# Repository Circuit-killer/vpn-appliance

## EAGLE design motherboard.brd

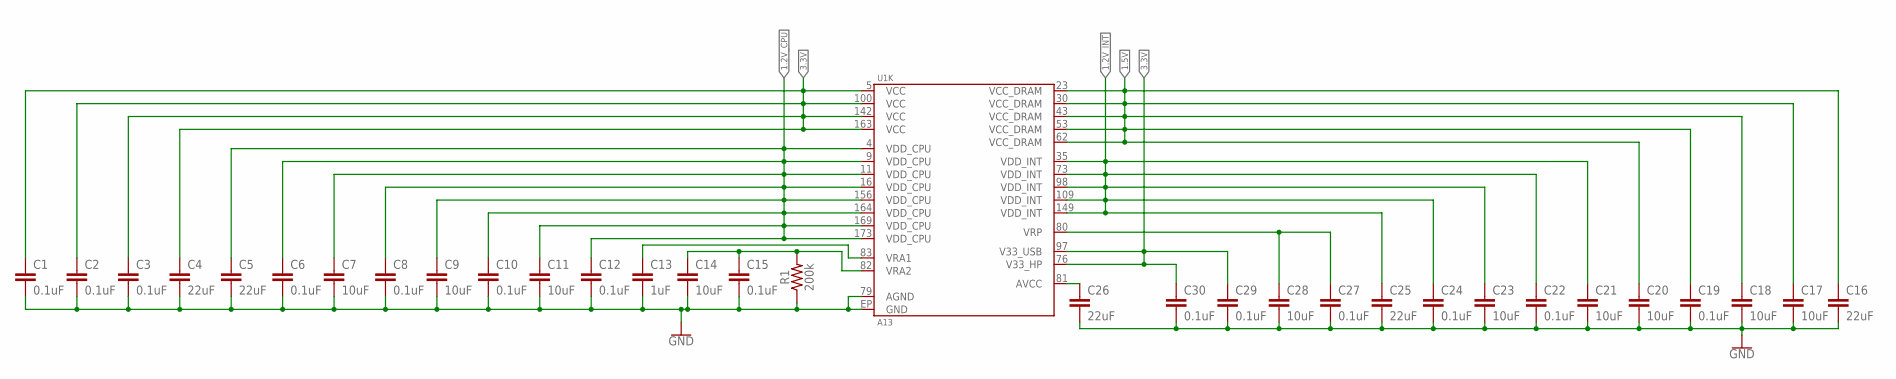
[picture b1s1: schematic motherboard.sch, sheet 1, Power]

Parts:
C1, C2, C3, C6, C8, C10, C12, C15, C19, C22, C24, C27, C29, C30: 0.1uF; 0603
C4, C5, C16, C25, C26: 22uF; 0603
C7, C9, C11, C14, C17, C18, C20, C21, C23, C28: 10uF; 0603
C13: 1uF; 0603
R1: 200k; 0603
U1: A13

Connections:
1.2V_CPU: C5.1, C6.1, C7.1, C8.1, C9.1, C10.1, C11.1, C12.1, U1.4 (VDD_CPU), U1.9 (VDD_CPU), U1.11 (VDD_CPU), U1.16 (VDD_CPU), U1.156 (VDD_CPU), U1.164 (VDD_CPU), U1.169 (VDD_CPU), U1.173 (VDD_CPU)
1.2V_INT: C21.1, C22.1, C23.1, C24.1, C25.1, U1.35 (VDD_INT), U1.73 (VDD_INT), U1.98 (VDD_INT), U1.109 (VDD_INT), U1.149 (VDD_INT)
1.5V: C16.1, C17.1, C18.1, C19.1, C20.1, U1.23 (VCC_DRAM), U1.30 (VCC_DRAM), U1.43 (VCC_DRAM), U1.53 (VCC_DRAM), U1.62 (VCC_DRAM); also elsewhere on the board
3.3V: C1.1, C2.1, C3.1, C4.1, C29.1, C30.1, U1.5 (VCC), U1.76 (V33_HP), U1.97 (V33_USB), U1.100 (VCC), U1.142 (VCC), U1.163 (VCC)
GND: C1.2, C2.2, C3.2, C4.2, C5.2, C6.2, C7.2, C8.2, C9.2, C10.2, C11.2, C12.2, C13.2, C14.2, C15.2, C16.2, C17.2, C18.2, C19.2, C20.2, C21.2, C22.2, C23.2, C24.2, C25.2, C26.2, C27.2, C28.2, C29.2, C30.2, R1.1, U1.79 (AGND), U1.EP (GND); also elsewhere on the board
unnamed: C13.1, U1.83 (VRA1)
unnamed: C14.1, C15.1, R1.2, U1.82 (VRA2)
unnamed: C26.1, U1.81 (AVCC)
unnamed: C27.1, C28.1, U1.80 (VRP)

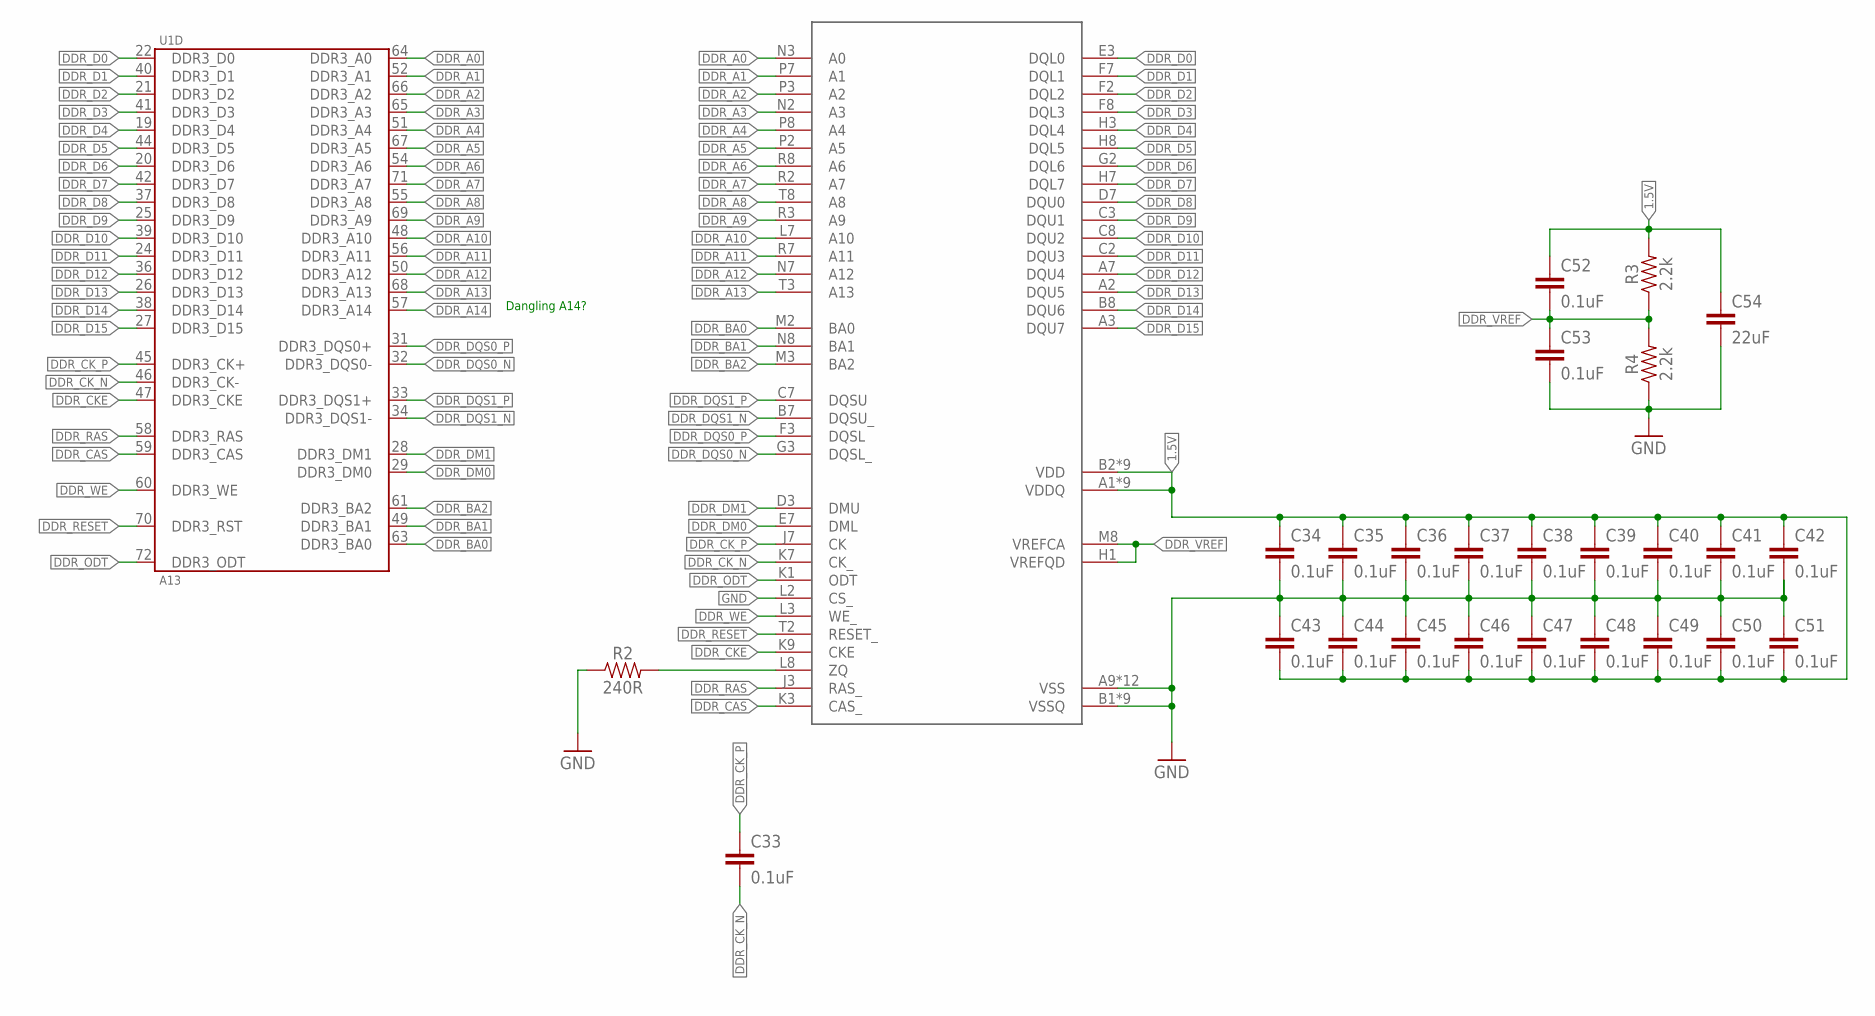
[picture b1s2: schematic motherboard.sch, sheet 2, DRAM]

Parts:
C33, C34, C35, C36, C37, C38, C39, C40, C41, C42, C43, C44, C45, C46, C47, C48, C49, C50, C51, C52, C53: 0.1uF; 0603
C54: 22uF; 0603
DRAM: AS4C128M16D3B-12BCN; FBGA96-6X16
R2: 240R; 0603
R3, R4: 2.2k; 0603
U1: A13

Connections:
1.5V: C34.1, C35.1, C36.1, C37.1, C38.1, C39.1, C40.1, C41.1, C42.1, C43.2, C44.2, C45.2, C46.2, C47.2, C48.2, C49.2, C50.2, C51.2, C52.1, C54.1, DRAM.A1 (VDDQ), DRAM.A8 (VDDQ), DRAM.B2 (VDD), DRAM.C1 (VDDQ), DRAM.C9 (VDDQ), DRAM.D2 (VDDQ), DRAM.D9 (VDD), DRAM.E9 (VDDQ), DRAM.F1 (VDDQ), DRAM.G7 (VDD), DRAM.H2 (VDDQ), DRAM.H9 (VDDQ), DRAM.K2 (VDD), DRAM.K8 (VDD), DRAM.N1 (VDD), DRAM.N9 (VDD), DRAM.R1 (VDD), DRAM.R9 (VDD), R3.2; also elsewhere on the board
DDR_A0: DRAM.N3 (A0), U1.64 (DDR3_A0)
DDR_A1: DRAM.P7 (A1), U1.52 (DDR3_A1)
DDR_A2: DRAM.P3 (A2), U1.66 (DDR3_A2)
DDR_A3: DRAM.N2 (A3), U1.65 (DDR3_A3)
DDR_A4: DRAM.P8 (A4), U1.51 (DDR3_A4)
DDR_A5: DRAM.P2 (A5), U1.67 (DDR3_A5)
DDR_A6: DRAM.R8 (A6), U1.54 (DDR3_A6)
DDR_A7: DRAM.R2 (A7), U1.71 (DDR3_A7)
DDR_A8: DRAM.T8 (A8), U1.55 (DDR3_A8)
DDR_A9: DRAM.R3 (A9), U1.69 (DDR3_A9)
DDR_A10: DRAM.L7 (A10), U1.48 (DDR3_A10)
DDR_A11: DRAM.R7 (A11), U1.56 (DDR3_A11)
DDR_A12: DRAM.N7 (A12), U1.50 (DDR3_A12)
DDR_A13: DRAM.T3 (A13), U1.68 (DDR3_A13)
DDR_A14: U1.57 (DDR3_A14)
DDR_BA0: DRAM.M2 (BA0), U1.63 (DDR3_BA0)
DDR_BA1: DRAM.N8 (BA1), U1.49 (DDR3_BA1)
DDR_BA2: DRAM.M3 (BA2), U1.61 (DDR3_BA2)
DDR_CAS: DRAM.K3 (CAS_), U1.59 (DDR3_CAS)
DDR_CKE: DRAM.K9 (CKE), U1.47 (DDR3_CKE)
DDR_CK_N: C33.2, DRAM.K7 (CK_), U1.46 (DDR3_CK-)
DDR_CK_P: C33.1, DRAM.J7 (CK), U1.45 (DDR3_CK+)
DDR_D0: DRAM.E3 (DQL0), U1.22 (DDR3_D0)
DDR_D1: DRAM.F7 (DQL1), U1.40 (DDR3_D1)
DDR_D2: DRAM.F2 (DQL2), U1.21 (DDR3_D2)
DDR_D3: DRAM.F8 (DQL3), U1.41 (DDR3_D3)
DDR_D4: DRAM.H3 (DQL4), U1.19 (DDR3_D4)
DDR_D5: DRAM.H8 (DQL5), U1.44 (DDR3_D5)
DDR_D6: DRAM.G2 (DQL6), U1.20 (DDR3_D6)
DDR_D7: DRAM.H7 (DQL7), U1.42 (DDR3_D7)
DDR_D8: DRAM.D7 (DQU0), U1.37 (DDR3_D8)
DDR_D9: DRAM.C3 (DQU1), U1.25 (DDR3_D9)
DDR_D10: DRAM.C8 (DQU2), U1.39 (DDR3_D10)
DDR_D11: DRAM.C2 (DQU3), U1.24 (DDR3_D11)
DDR_D12: DRAM.A7 (DQU4), U1.36 (DDR3_D12)
DDR_D13: DRAM.A2 (DQU5), U1.26 (DDR3_D13)
DDR_D14: DRAM.B8 (DQU6), U1.38 (DDR3_D14)
DDR_D15: DRAM.A3 (DQU7), U1.27 (DDR3_D15)
DDR_DM0: DRAM.E7 (DML), U1.29 (DDR3_DM0)
DDR_DM1: DRAM.D3 (DMU), U1.28 (DDR3_DM1)
DDR_DQS0_N: DRAM.G3 (DQSL_), U1.32 (DDR3_DQS0-)
DDR_DQS0_P: DRAM.F3 (DQSL), U1.31 (DDR3_DQS0+)
DDR_DQS1_N: DRAM.B7 (DQSU_), U1.34 (DDR3_DQS1-)
DDR_DQS1_P: DRAM.C7 (DQSU), U1.33 (DDR3_DQS1+)
DDR_ODT: DRAM.K1 (ODT), U1.72 (DDR3_ODT)
DDR_RAS: DRAM.J3 (RAS_), U1.58 (DDR3_RAS)
DDR_RESET: DRAM.T2 (RESET_), U1.70 (DDR3_RST)
DDR_VREF: C52.2, C53.1, DRAM.H1 (VREFQD), DRAM.M8 (VREFCA), R3.1, R4.2
DDR_WE: DRAM.L3 (WE_), U1.60 (DDR3_WE)
GND: C34.2, C35.2, C36.2, C37.2, C38.2, C39.2, C40.2, C41.2, C42.2, C43.1, C44.1, C45.1, C46.1, C47.1, C48.1, C49.1, C50.1, C51.1, C53.2, C54.2, DRAM.A9 (VSS), DRAM.B1 (VSSQ), DRAM.B3 (VSS), DRAM.B9 (VSSQ), DRAM.D1 (VSSQ), DRAM.D8 (VSSQ), DRAM.E1 (VSS), DRAM.E2 (VSSQ), DRAM.E8 (VSSQ), DRAM.F9 (VSSQ), DRAM.G1 (VSSQ), DRAM.G8 (VSS), DRAM.G9 (VSSQ), DRAM.J2 (VSS), DRAM.J8 (VSS), DRAM.L2 (CS_), DRAM.M1 (VSS), DRAM.M9 (VSS), DRAM.P1 (VSS), DRAM.P9 (VSS), DRAM.T1 (VSS), DRAM.T9 (VSS), R2.1, R4.1; also elsewhere on the board
ZQ: DRAM.L8 (ZQ), R2.2

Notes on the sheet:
Dangling A14?

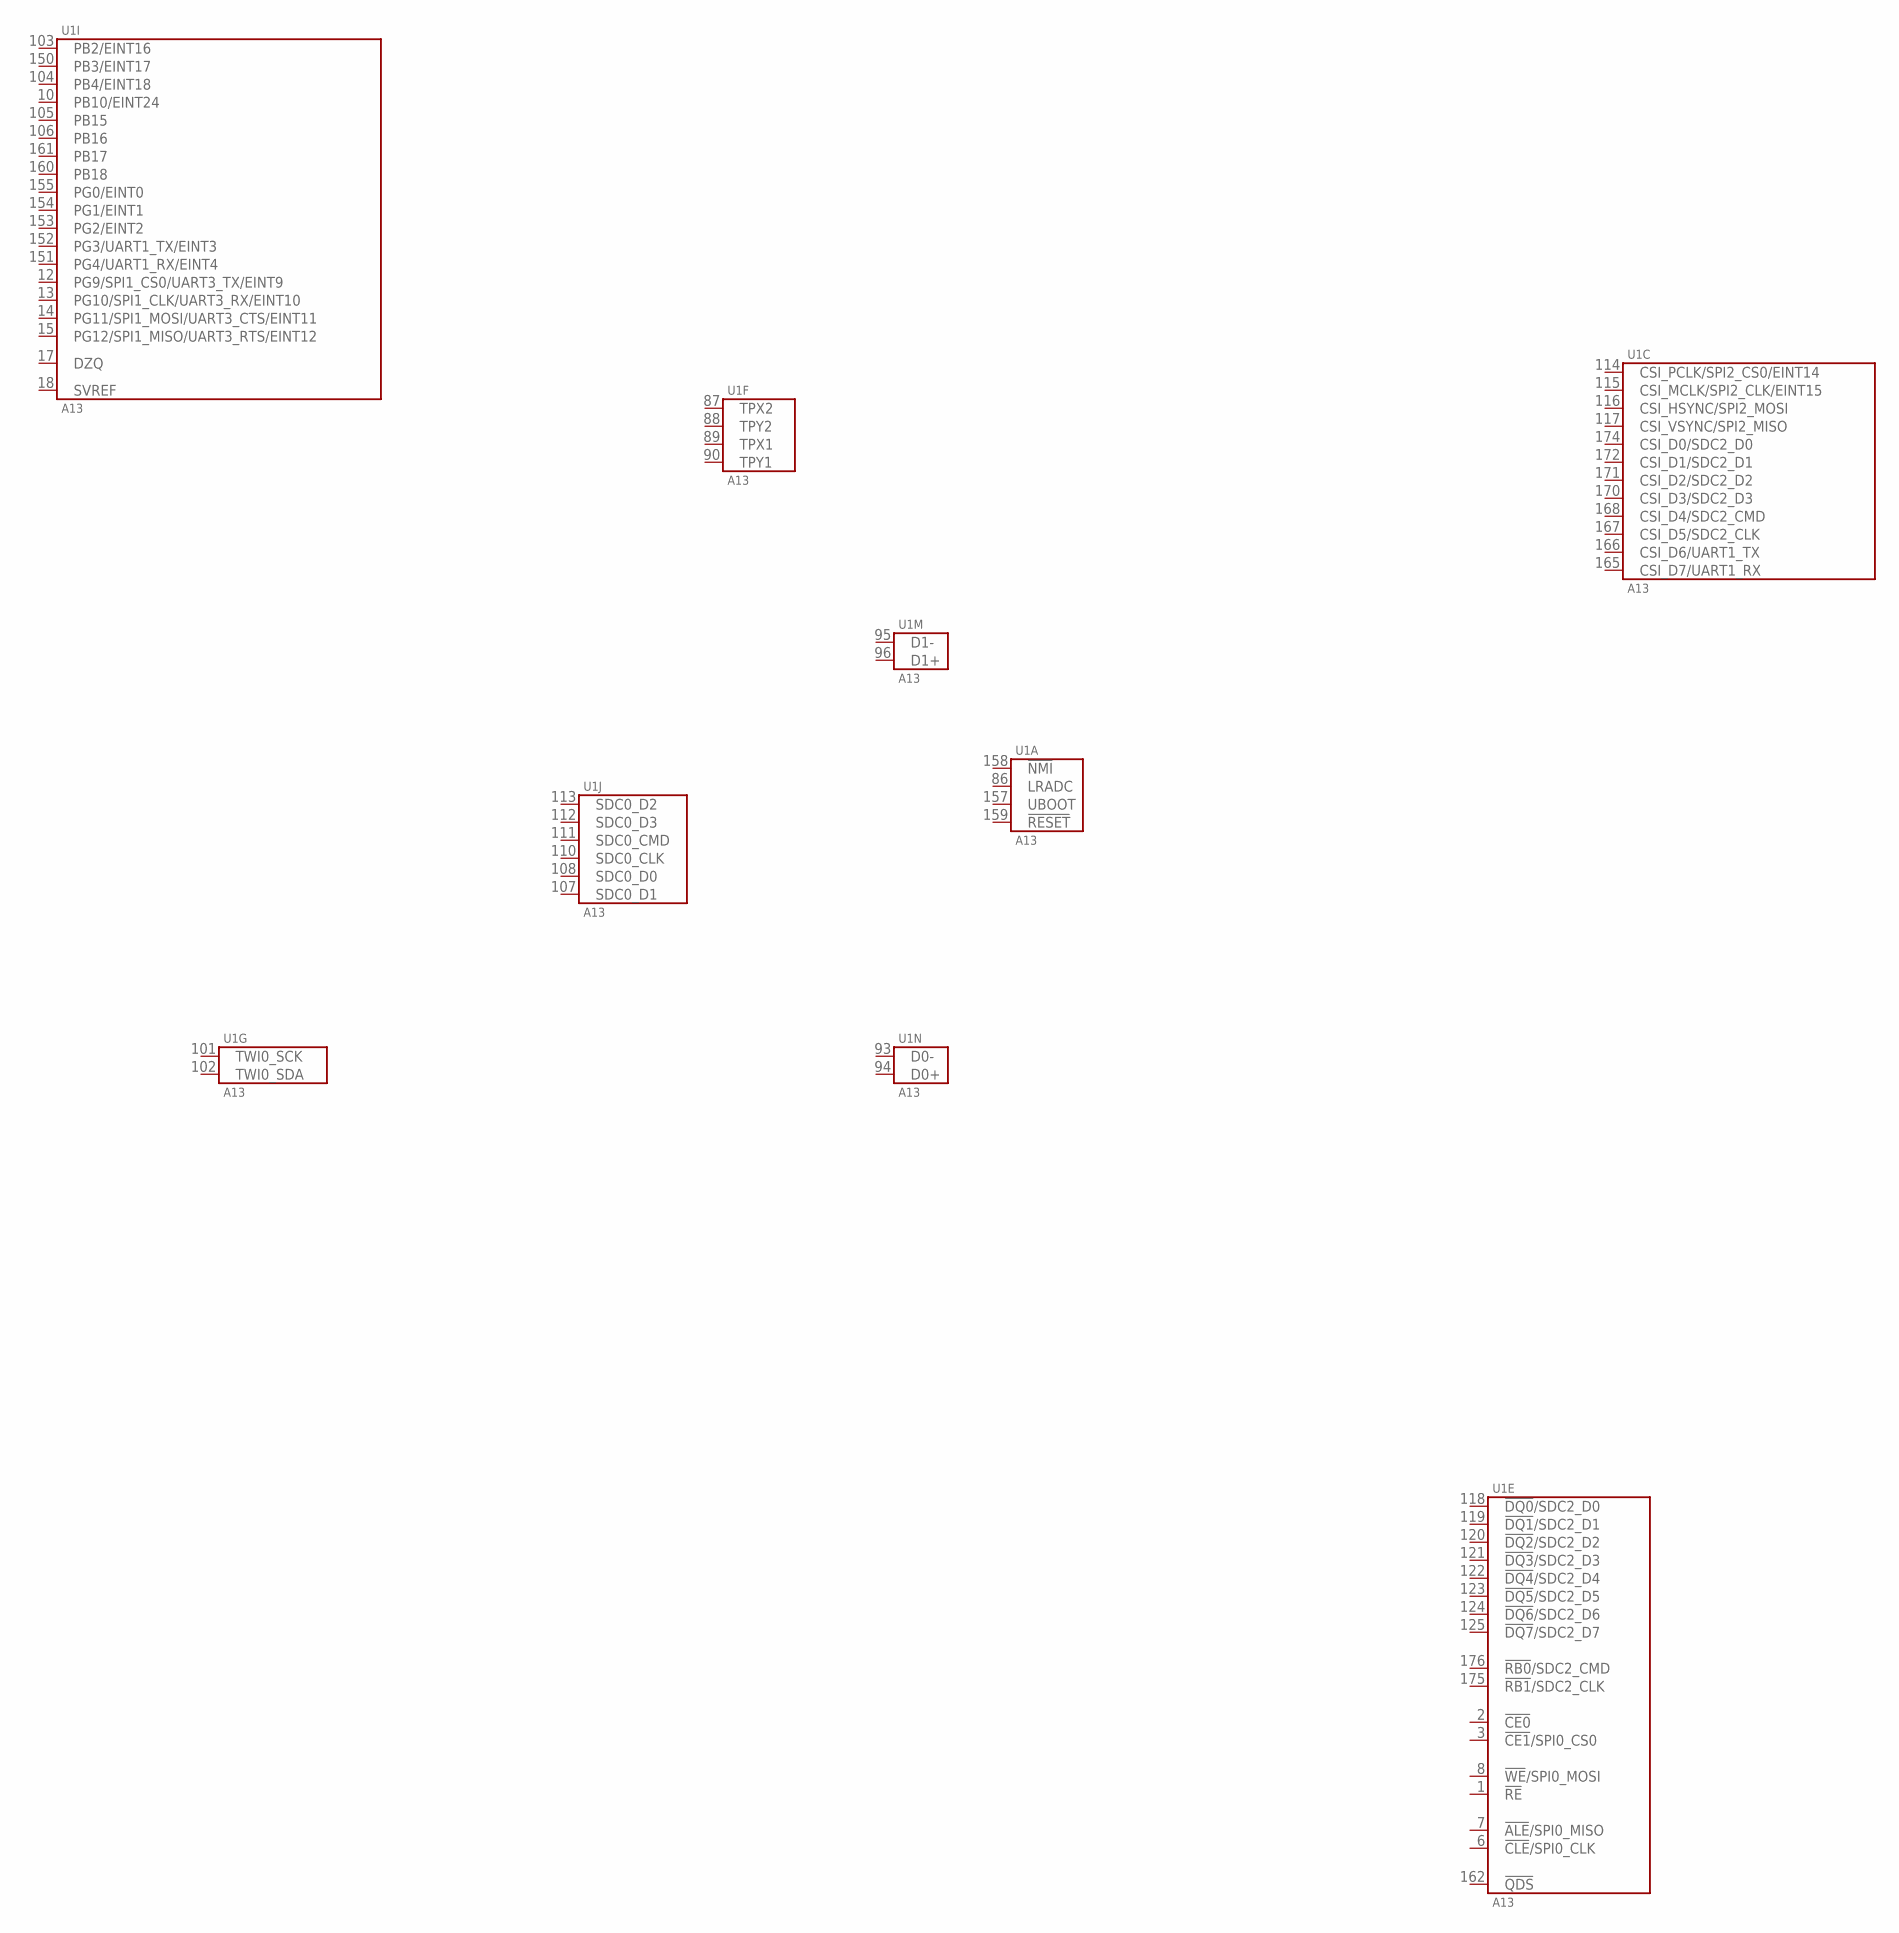
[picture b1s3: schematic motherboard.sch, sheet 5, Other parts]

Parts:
U1: A13

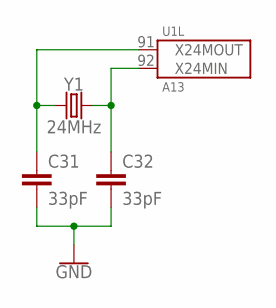
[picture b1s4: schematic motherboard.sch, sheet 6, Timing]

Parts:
C31, C32: 33pF; 0603
U1: A13
Y1: 24MHz; CRYSTAL-SMD-5X3.2-4PAD

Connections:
GND: C31.2, C32.2; also elsewhere on the board
unnamed: C32.1, U1.92 (X24MIN), Y1.3 (2)
unnamed: C31.1, U1.91 (X24MOUT), Y1.1

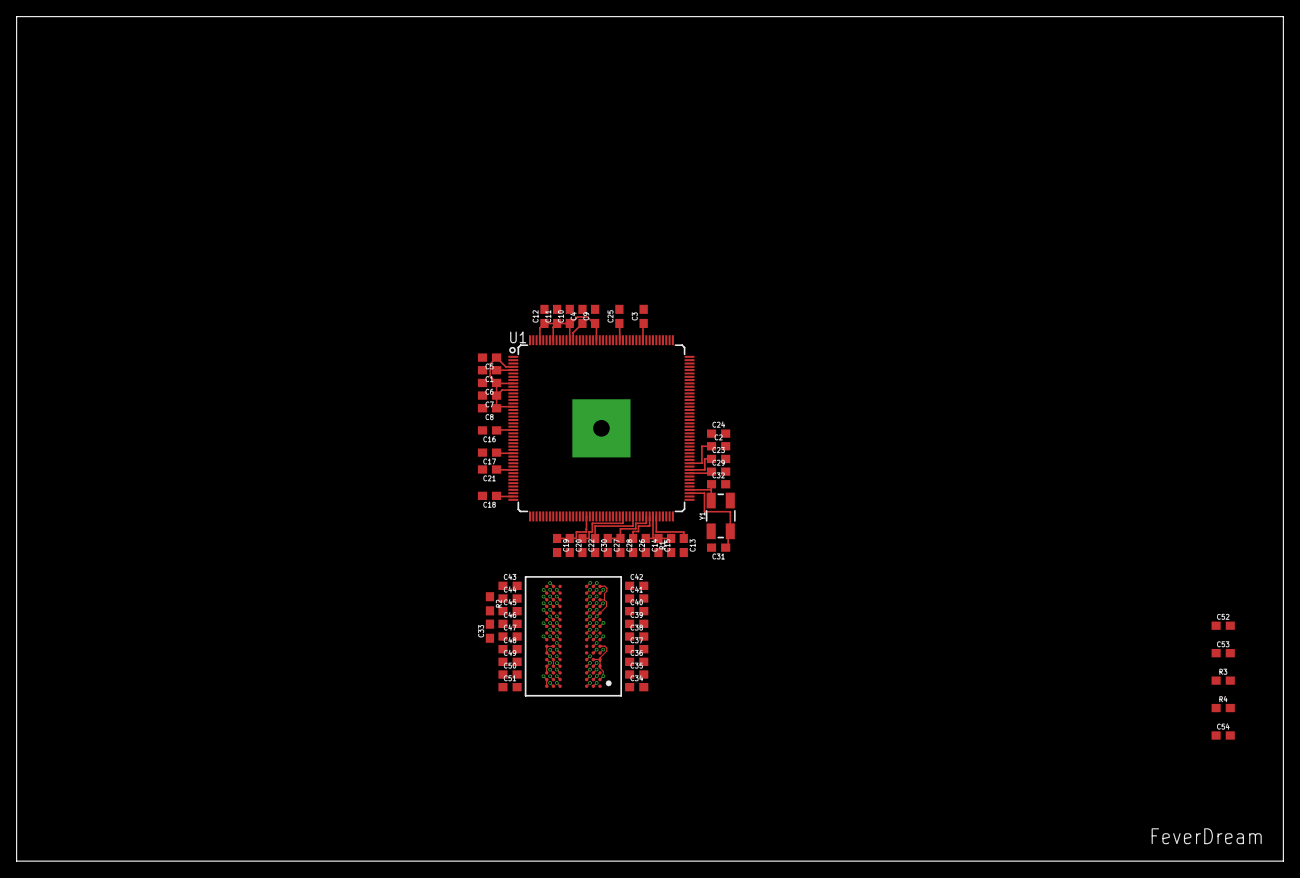
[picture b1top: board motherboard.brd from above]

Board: 4 copper layers, 152.4 x 101.6 mm, 61 parts (0 on the bottom side), 60 nets.

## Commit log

2018-05-06 Routing BGAs by hand feels like a terrifying fever dream.
2018-05-06 The feverdream continues unabated.

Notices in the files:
parts and their libraries:
SparkFun-Capacitors: Licensing: Creative Commons ShareAlike 4.0 International - https://creativecommons.org/licenses/by-sa/4.0
